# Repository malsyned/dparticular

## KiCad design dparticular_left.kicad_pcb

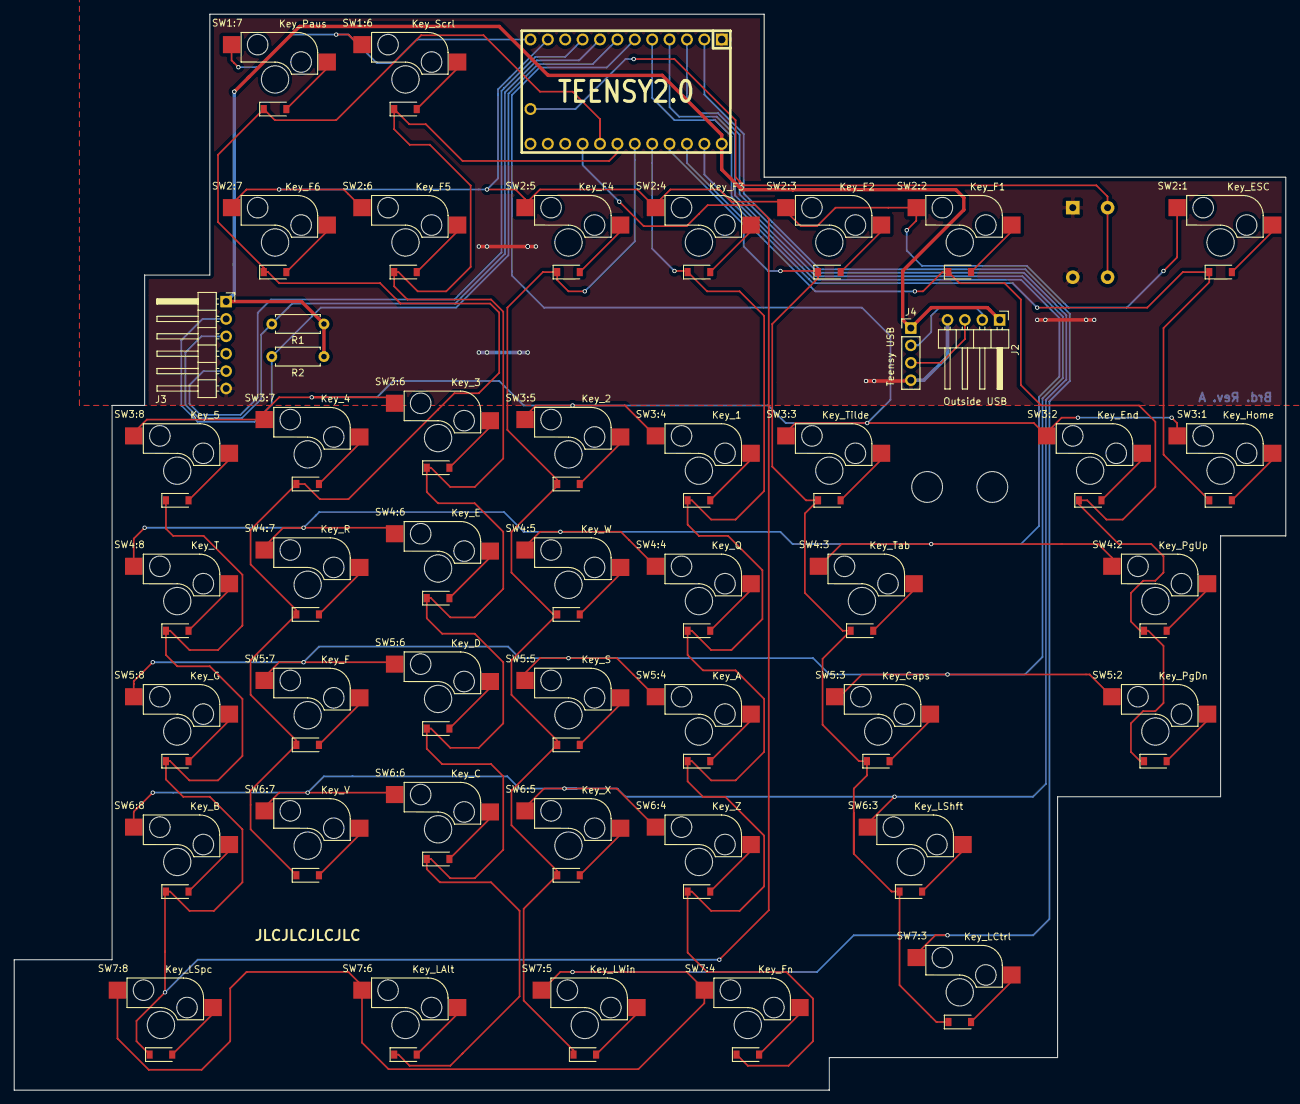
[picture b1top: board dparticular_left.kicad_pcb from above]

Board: 2 copper layers, 185.7 x 157.2 mm, 51 parts (1 on the bottom side), 65 nets.

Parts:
H1: USB Strain L; MountingHole_4.5mm
H2: USB Strain R; MountingHole_4.5mm
J2: Outside USB; PinHeader_1x04_P2.54mm_Horizontal
J3: To Right Hand; PinHeader_1x06_P2.54mm_Horizontal
J4: Teensy USB; PinHeader_1x04_P2.54mm_Vertical
R1, R2: 4.7k; R_Axial_DIN0207_L6.3mm_D2.5mm_P7.62mm_Horizontal
SW1: Reset; JB15KP-2A
SW1:6: Key_Scrl; MX_W_DIODE
SW1:7: Key_Paus; MX_W_DIODE
SW2:1: Key_ESC; MX_W_DIODE
SW2:2: Key_F1; MX_W_DIODE
SW2:3: Key_F2; MX_W_DIODE
SW2:4: Key_F3; MX_W_DIODE
SW2:5: Key_F4; MX_W_DIODE
SW2:6: Key_F5; MX_W_DIODE
SW2:7: Key_F6; MX_W_DIODE
SW3:1: Key_Home; MX_W_DIODE
SW3:2: Key_End; MX_W_DIODE
SW3:3: Key_Tilde; MX_W_DIODE
SW3:4: Key_1; MX_W_DIODE
SW3:5: Key_2; MX_W_DIODE
SW3:6: Key_3; MX_W_DIODE
SW3:7: Key_4; MX_W_DIODE
SW3:8: Key_5; MX_W_DIODE
SW4:2: Key_PgUp; MX_W_DIODE
SW4:3: Key_Tab; MX_W_DIODE
SW4:4: Key_Q; MX_W_DIODE
SW4:5: Key_W; MX_W_DIODE
SW4:6: Key_E; MX_W_DIODE
SW4:7: Key_R; MX_W_DIODE
SW4:8: Key_T; MX_W_DIODE
SW5:2: Key_PgDn; MX_W_DIODE
SW5:3: Key_Caps; MX_W_DIODE
SW5:4: Key_A; MX_W_DIODE
SW5:5: Key_S; MX_W_DIODE
SW5:6: Key_D; MX_W_DIODE
SW5:7: Key_F; MX_W_DIODE
SW5:8: Key_G; MX_W_DIODE
SW6:3: Key_LShft; MX_W_DIODE
SW6:4: Key_Z; MX_W_DIODE
SW6:5: Key_X; MX_W_DIODE
SW6:6: Key_C; MX_W_DIODE
SW6:7: Key_V; MX_W_DIODE
SW6:8: Key_B; MX_W_DIODE
SW7:3: Key_LCtrl; MX_W_DIODE
SW7:4: Key_Fn; MX_W_DIODE
SW7:5: Key_LWin; MX_W_DIODE
SW7:6: Key_LAlt; MX_W_DIODE
SW7:8: Key_LSpc; MX_W_DIODE
U2: TEENSY2.0; TEENSY_2.0_EDGES_ONLY

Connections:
+5V: J2.1, J3.1, J4.1, R1.1, R2.1, U2.29
/COL1: SW2:1.4, SW3:1.4, U2.28
/COL2: SW2:2.4, SW3:2.4, SW4:2.4, SW5:2.4, U2.27
/COL3: SW2:3.4, SW3:3.4, SW4:3.4, SW5:3.4, SW6:3.4, SW7:3.4, U2.26
/COL4: SW2:4.4, SW3:4.4, SW4:4.4, SW5:4.4, SW6:4.4, SW7:4.4, U2.25
/COL5: SW2:5.4, SW3:5.4, SW4:5.4, SW5:5.4, SW6:5.4, SW7:5.4, U2.24
/COL6: SW1:6.4, SW2:6.4, SW3:6.4, SW4:6.4, SW5:6.4, SW6:6.4, SW7:6.4, U2.23
/COL7: SW1:7.4, SW2:7.4, SW3:7.4, SW4:7.4, SW5:7.4, SW6:7.4, U2.22
/COL8: SW3:8.4, SW4:8.4, SW5:8.4, SW6:8.4, SW7:8.4, U2.21
/LED_D: J3.5, U2.9
/ROW1: SW1:6.1, SW1:7.1, U2.12
/ROW2: SW2:1.1, SW2:2.1, SW2:3.1, SW2:4.1, SW2:5.1, SW2:6.1, SW2:7.1, U2.11
/ROW3: SW3:1.1, SW3:2.1, SW3:3.1, SW3:4.1, SW3:5.1, SW3:6.1, SW3:7.1, SW3:8.1, U2.6
/ROW4: SW4:2.1, SW4:3.1, SW4:4.1, SW4:5.1, SW4:6.1, SW4:7.1, SW4:8.1, U2.5
/ROW5: SW5:2.1, SW5:3.1, SW5:4.1, SW5:5.1, SW5:6.1, SW5:7.1, SW5:8.1, U2.4
/ROW6: SW6:3.1, SW6:4.1, SW6:5.1, SW6:6.1, SW6:7.1, SW6:8.1, U2.3
/ROW7: SW7:3.1, SW7:4.1, SW7:5.1, SW7:6.1, SW7:8.1, U2.2
/SCL: J3.2, R2.2, U2.7
/SDA: J3.3, R1.2, U2.8
/USB_DN: J2.2, J4.2
/USB_DP: J2.3, J4.3
GND: J2.4, J3.6, J4.4, SW1.1, SW1.2, U2.1
unnamed: SW1.3, SW1.4, U2.16
unnamed: SW1:6.2, SW1:6.3
unnamed: SW1:7.2, SW1:7.3
unnamed: SW2:1.2, SW2:1.3
unnamed: SW2:2.2, SW2:2.3
unnamed: SW2:3.2, SW2:3.3
unnamed: SW2:4.2, SW2:4.3
unnamed: SW2:5.2, SW2:5.3
unnamed: SW2:6.2, SW2:6.3
unnamed: SW2:7.2, SW2:7.3
unnamed: SW3:1.2, SW3:1.3
unnamed: SW3:2.2, SW3:2.3
unnamed: SW3:3.2, SW3:3.3
unnamed: SW3:4.2, SW3:4.3
unnamed: SW3:5.2, SW3:5.3
unnamed: SW3:6.2, SW3:6.3
unnamed: SW3:7.2, SW3:7.3
unnamed: SW3:8.2, SW3:8.3
unnamed: SW4:2.2, SW4:2.3
unnamed: SW4:3.2, SW4:3.3
unnamed: SW4:4.2, SW4:4.3
unnamed: SW4:5.2, SW4:5.3
unnamed: SW4:6.2, SW4:6.3
unnamed: SW4:7.2, SW4:7.3
unnamed: SW4:8.2, SW4:8.3
unnamed: SW5:2.2, SW5:2.3
unnamed: SW5:3.2, SW5:3.3
unnamed: SW5:4.2, SW5:4.3
unnamed: SW5:5.2, SW5:5.3
unnamed: SW5:6.2, SW5:6.3
unnamed: SW5:7.2, SW5:7.3
unnamed: SW5:8.2, SW5:8.3
unnamed: SW6:3.2, SW6:3.3
unnamed: SW6:4.2, SW6:4.3
unnamed: SW6:5.2, SW6:5.3
unnamed: SW6:6.2, SW6:6.3
unnamed: SW6:7.2, SW6:7.3
unnamed: SW6:8.2, SW6:8.3
unnamed: SW7:3.2, SW7:3.3
unnamed: SW7:4.2, SW7:4.3
unnamed: SW7:5.2, SW7:5.3
unnamed: SW7:6.2, SW7:6.3
unnamed: SW7:8.2, SW7:8.3

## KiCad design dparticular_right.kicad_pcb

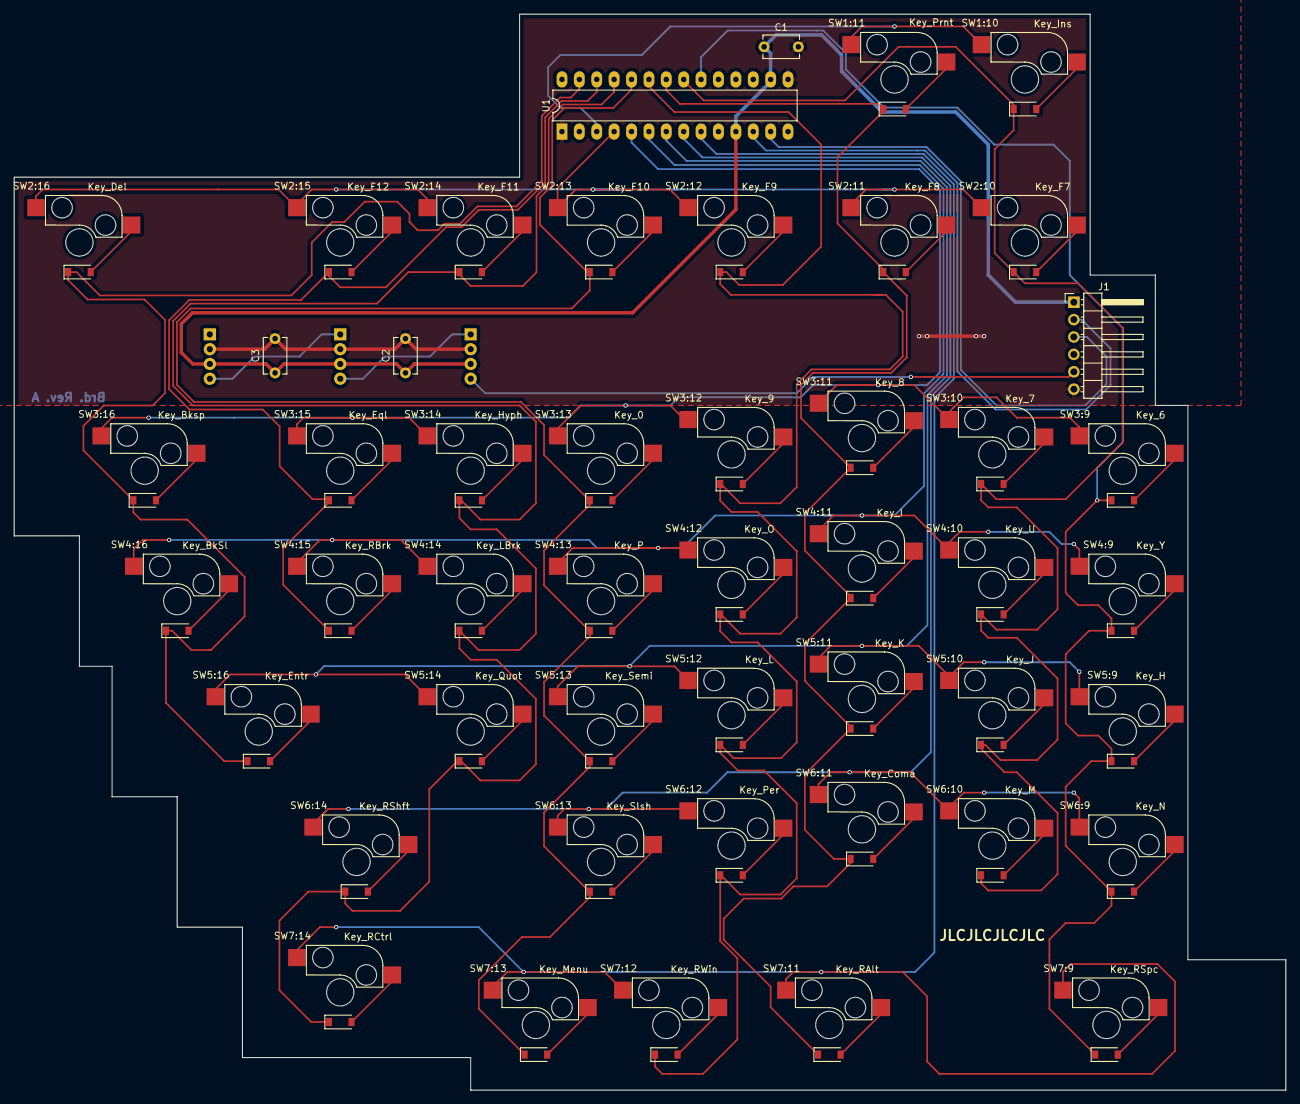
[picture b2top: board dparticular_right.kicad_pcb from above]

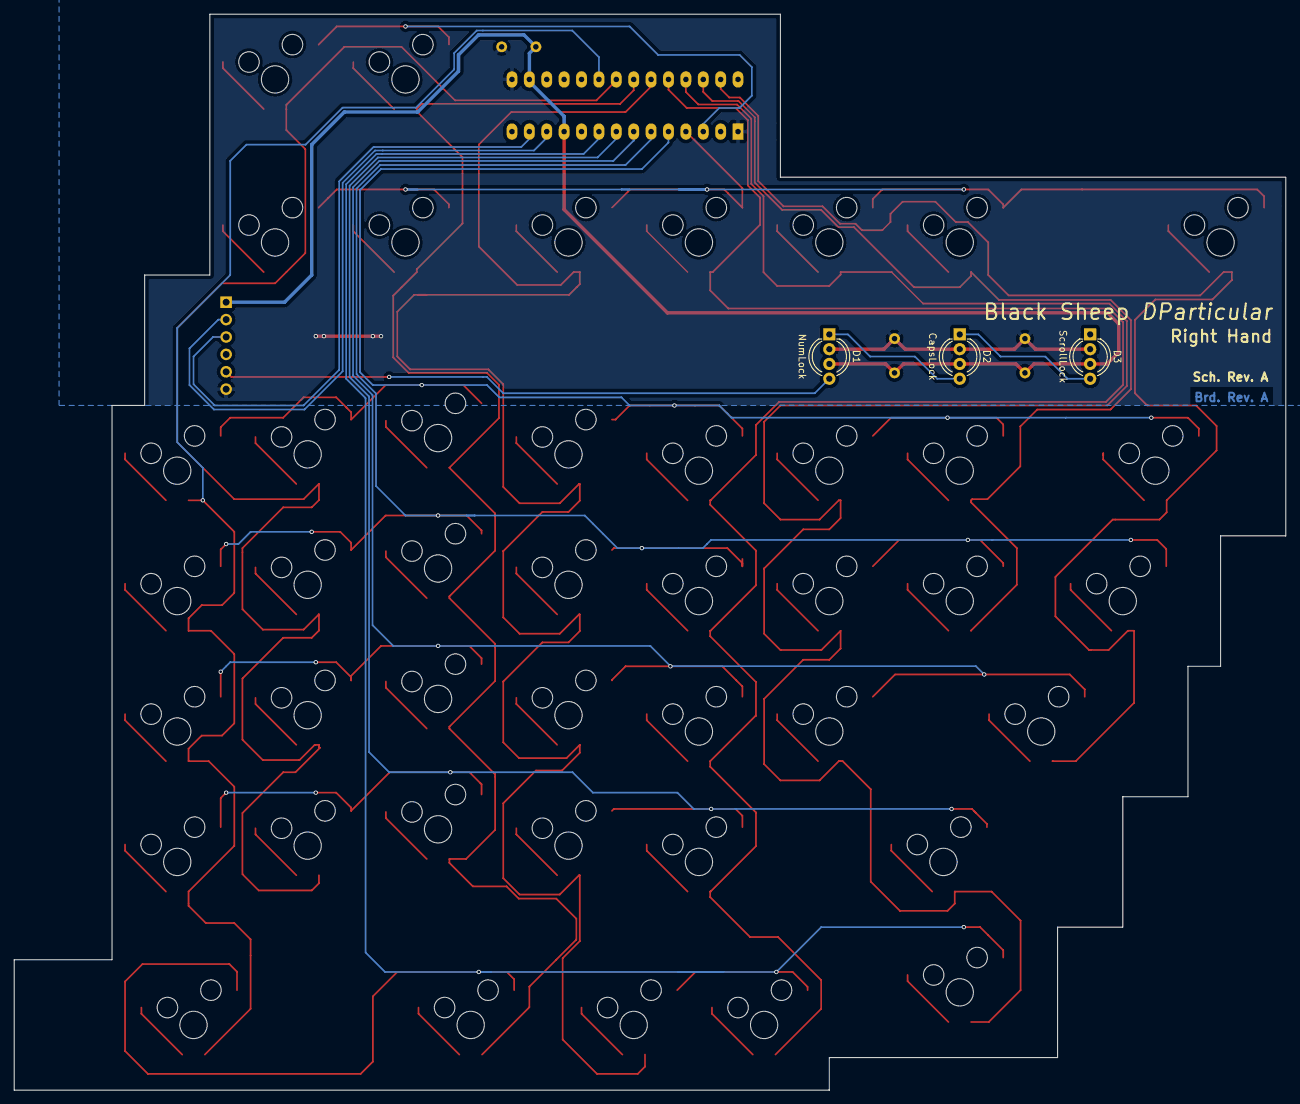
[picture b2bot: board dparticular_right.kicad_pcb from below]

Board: 2 copper layers, 185.7 x 157.2 mm, 51 parts (3 on the bottom side), 65 nets.

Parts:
C1, C2, C3: 0.1uF; C_Disc_D5.1mm_W3.2mm_P5.00mm
D1: NumLock; LED_D5.0mm-4_RGB_Wide_Pins
D2: CapsLock; LED_D5.0mm-4_RGB_Wide_Pins
D3: ScrollLock; LED_D5.0mm-4_RGB_Wide_Pins
J1: To Left Hand; PinHeader_1x06_P2.54mm_Horizontal
SW1:10: Key_Ins; MX_W_DIODE
SW1:11: Key_Prnt; MX_W_DIODE
SW2:10: Key_F7; MX_W_DIODE
SW2:11: Key_F8; MX_W_DIODE
SW2:12: Key_F9; MX_W_DIODE
SW2:13: Key_F10; MX_W_DIODE
SW2:14: Key_F11; MX_W_DIODE
SW2:15: Key_F12; MX_W_DIODE
SW2:16: Key_Del; MX_W_DIODE
SW3:9: Key_6; MX_W_DIODE
SW3:10: Key_7; MX_W_DIODE
SW3:11: Key_8; MX_W_DIODE
SW3:12: Key_9; MX_W_DIODE
SW3:13: Key_0; MX_W_DIODE
SW3:14: Key_Hyph; MX_W_DIODE
SW3:15: Key_Eql; MX_W_DIODE
SW3:16: Key_Bksp; MX_W_DIODE
SW4:9: Key_Y; MX_W_DIODE
SW4:10: Key_U; MX_W_DIODE
SW4:11: Key_I; MX_W_DIODE
SW4:12: Key_O; MX_W_DIODE
SW4:13: Key_P; MX_W_DIODE
SW4:14: Key_LBrk; MX_W_DIODE
SW4:15: Key_RBrk; MX_W_DIODE
SW4:16: Key_BkSl; MX_W_DIODE
SW5:9: Key_H; MX_W_DIODE
SW5:10: Key_J; MX_W_DIODE
SW5:11: Key_K; MX_W_DIODE
SW5:12: Key_L; MX_W_DIODE
SW5:13: Key_Semi; MX_W_DIODE
SW5:14: Key_Quot; MX_W_DIODE
SW5:16: Key_Entr; MX_W_DIODE
SW6:9: Key_N; MX_W_DIODE
SW6:10: Key_M; MX_W_DIODE
SW6:11: Key_Coma; MX_W_DIODE
SW6:12: Key_Per; MX_W_DIODE
SW6:13: Key_Slsh; MX_W_DIODE
SW6:14: Key_RShft; MX_W_DIODE
SW7:9: Key_RSpc; MX_W_DIODE
SW7:11: Key_RAlt; MX_W_DIODE
SW7:12: Key_RWin; MX_W_DIODE
SW7:13: Key_Menu; MX_W_DIODE
SW7:14: Key_RCtrl; MX_W_DIODE
U1: MCP23018; DIP-28_W7.62mm_LongPads

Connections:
+5V: C1.1, C2.1, C3.1, D1.3, D2.3, D3.3, J1.1, U1.11, U1.16
/COL9: SW3:9.4, SW4:9.4, SW5:9.4, SW6:9.4, SW7:9.4, U1.20
/COL10: SW1:10.4, SW2:10.4, SW3:10.4, SW4:10.4, SW5:10.4, SW6:10.4, U1.21
/COL11: SW1:11.4, SW2:11.4, SW3:11.4, SW4:11.4, SW5:11.4, SW6:11.4, SW7:11.4, U1.22
/COL12: SW2:12.4, SW3:12.4, SW4:12.4, SW5:12.4, SW6:12.4, SW7:12.4, U1.23
/COL13: SW2:13.4, SW3:13.4, SW4:13.4, SW5:13.4, SW6:13.4, SW7:13.4, U1.24
/COL14: SW2:14.4, SW3:14.4, SW4:14.4, SW5:14.4, SW6:14.4, SW7:14.4, U1.25
/COL15: SW2:15.4, SW3:15.4, SW4:15.4, U1.26
/COL16: SW2:16.4, SW3:16.4, SW4:16.4, SW5:16.4, U1.27
/LED_D: D1.4, J1.5
/ROW1: SW1:10.1, SW1:11.1, U1.3
/ROW2: SW2:10.1, SW2:11.1, SW2:12.1, SW2:13.1, SW2:14.1, SW2:15.1, SW2:16.1, U1.4
/ROW3: SW3:9.1, SW3:10.1, SW3:11.1, SW3:12.1, SW3:13.1, SW3:14.1, SW3:15.1, SW3:16.1, U1.5
/ROW4: SW4:9.1, SW4:10.1, SW4:11.1, SW4:12.1, SW4:13.1, SW4:14.1, SW4:15.1, SW4:16.1, U1.6
/ROW5: SW5:9.1, SW5:10.1, SW5:11.1, SW5:12.1, SW5:13.1, SW5:14.1, SW5:16.1, U1.7
/ROW6: SW6:9.1, SW6:10.1, SW6:11.1, SW6:12.1, SW6:13.1, SW6:14.1, U1.8
/ROW7: SW7:9.1, SW7:11.1, SW7:12.1, SW7:13.1, SW7:14.1, U1.9
/SCL: J1.2, U1.12
/SDA: J1.3, U1.13
GND: C1.2, C2.2, C3.2, D1.2, D2.2, D3.2, J1.6, U1.1, U1.15
unnamed: D1.1, D2.4
unnamed: D2.1, D3.4
unnamed: SW1:10.2, SW1:10.3
unnamed: SW1:11.2, SW1:11.3
unnamed: SW2:10.2, SW2:10.3
unnamed: SW2:11.2, SW2:11.3
unnamed: SW2:12.2, SW2:12.3
unnamed: SW2:13.2, SW2:13.3
unnamed: SW2:14.2, SW2:14.3
unnamed: SW2:15.2, SW2:15.3
unnamed: SW2:16.2, SW2:16.3
unnamed: SW3:9.2, SW3:9.3
unnamed: SW3:10.2, SW3:10.3
unnamed: SW3:11.2, SW3:11.3
unnamed: SW3:12.2, SW3:12.3
unnamed: SW3:13.2, SW3:13.3
unnamed: SW3:14.2, SW3:14.3
unnamed: SW3:15.2, SW3:15.3
unnamed: SW3:16.2, SW3:16.3
unnamed: SW4:9.2, SW4:9.3
unnamed: SW4:10.2, SW4:10.3
unnamed: SW4:11.2, SW4:11.3
unnamed: SW4:12.2, SW4:12.3
unnamed: SW4:13.2, SW4:13.3
unnamed: SW4:14.2, SW4:14.3
unnamed: SW4:15.2, SW4:15.3
unnamed: SW4:16.2, SW4:16.3
unnamed: SW5:9.2, SW5:9.3
unnamed: SW5:10.2, SW5:10.3
unnamed: SW5:11.2, SW5:11.3
unnamed: SW5:12.2, SW5:12.3
unnamed: SW5:13.2, SW5:13.3
unnamed: SW5:14.2, SW5:14.3
unnamed: SW5:16.2, SW5:16.3
unnamed: SW6:9.2, SW6:9.3
unnamed: SW6:10.2, SW6:10.3
unnamed: SW6:11.2, SW6:11.3
unnamed: SW6:12.2, SW6:12.3
unnamed: SW6:13.2, SW6:13.3
unnamed: SW6:14.2, SW6:14.3
unnamed: SW7:9.2, SW7:9.3
unnamed: SW7:11.2, SW7:11.3
unnamed: SW7:12.2, SW7:12.3
unnamed: SW7:13.2, SW7:13.3
unnamed: SW7:14.2, SW7:14.3

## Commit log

2020-06-24 DParticular initial commit, incomplete schematic
2020-07-01 Complete rough schematic
2020-07-06 Add enclosure 3D model
2020-07-06 Schematic revisions; first attempt at layout
2020-07-07 Beginning of separate right board project
2020-07-07 Preliminary placements for right hand
2020-07-07 Preliminary placements for left hand
2020-07-07 Deleted combined net and pcb
2020-07-07 Fixed footprints on switches and headers
2020-07-07 Edge cuts, net list exports
2020-07-07 .gitignore: kicad autosave files
2020-07-07 LED orientation and wiring
2020-07-08 LED labeling, schematic cosmetics
2020-07-08 Design rules compatible with common prototype board manufacturers
    Maximums that work with JLCPCB, ALLPCB, and Elecrow
2020-07-08 right hand PCB: Column traces
2020-07-08 Fix LED name order
2020-07-09 Right hand completed layout
2020-07-09 Left hand: updated solder mask design rules
2020-07-09 Moved USB headers to reduce width of top rectangle
2020-07-09 Remove .net files from repository
2020-07-09 Right hand: don't run traces between pads
2020-07-09 Right hand: eliminate right angles in columns 9 and 10
2020-07-09 Right hand: eliminate right angles in remaining columns
2020-07-09 Right hand: Eliminate all remaining right angles
2020-07-09 MX_W_DIODE: Cleaned up silk screen for hot plug socket
2020-07-09 Left hand: Changed uC pin assignments; Routed diode tracks and power rail
2020-07-09 Left hand: Routed columns
2020-07-09 Left hand: Completed routing
2020-07-09 Left hand: Cleaned up ground paths
2020-07-10 enclosure: 1/16" margin around PCBs
2020-07-10 enclosure: clean up inner edge
2020-07-10 enclosure: tweaked palm rest dimensions and rear margin
2020-07-10 enclosure: screw position sketch
2020-07-10 enclosure: threaded inserts
2020-07-10 enclosure: screw cutout cylinders
2020-07-10 enclosure: solid plate with screw holes
2020-07-10 Right hand pcb: Move LEDs half a key to the left
    This let's them be more visible between keycaps from a shallow viewing
    angle.
2020-07-10 Right hand PCB: Move traces farther away from drill holes
2020-07-14 PCBs: 3D models for Teensy 2.0 and MX sockets & diodes
2020-07-14 Left Hand PCB: Remove 3D header for Teensy USB solder points
2020-07-18 Left hand PCB: match fill zone size to right hand
2020-07-18 Teensy 2.0 Footprint: Assemble 3D model from upstream components
2020-07-18 MX_W_DIODE: Tweak socket 3D model scaling to compensate for upstream error
2020-07-19 enclosure: actually solid plate with screw holes
2020-07-19 enclosure: plate: clearance and corner radius
2020-07-19 enclosure: store distance from screw to edges in spreadsheet
2020-07-19 enclosure: threaded insert drill guides
2020-07-19 enclosure: Right top solid with drill holes
2020-07-19 enclosure: import and position latest PCB STEP files
2020-07-19 enclosure: mirror right solid plate and top to left half
2020-07-19 enclosure: holes in top and plate for lock status LEDs
    The offset of the centers from the F-keys row was hand-calculated by
    examining both the PCB layout and the footprint for the LED in question.
    If that part of the PCB layout changes, this will have to be
    hand-recomputed.
2020-07-19 enclosure: round outside edges of top pieces
    I removed the PCBs in this commit as well. Some STEP setting on my
    desktop was causing them to be huge and Github was throwing warnings.
2020-07-19 enclosure: Cutouts in plates and tops
2020-07-21 enclosure: adjust border after pleather experiments
2020-07-22 Left PCB: Mounting holes for USB strain relief zip ties
2020-07-25 Left Hand PCB: Reset switch for Teensy 2.0
2020-07-25 Left Hand PCB: Shorter switch, properly positioned
2020-07-26 Teensy 2.0 3D Model: Single pin (RST) connector for back edge
2020-07-26 Left Hand PCB: Move traces out from under Reset switch
2020-07-26 Reset Switch: Use schematic symbol with correct pinout
2020-07-26 enclosure: Reset switch cuts in left plate and top
2020-07-26 Reset Switch: Move between ESC and F1
2020-07-26 Right Hand PCB: Make some space for potential future drill holes
2020-07-27 enclosure: Adjust margins and enclosure width
    The front margin is reduced from 0.33" to 0.25"
    The side margin is moved and increased to fit potential future arrow keys
    The enclosure wall width is decreased from 3/8" to 1/4"
2020-07-28 enclosure: give the left half mirror a real name
2020-07-28 enclosure: Add flat face to front edge
2020-07-28 enclosure: initial sketch of palm pad pockets
2020-07-28 enclosure palm pad cuts: round corners
2020-07-30 Right Hand PCB: Moved LEDs half a key right and centered them vertically
    I made this change after discovering that, head on in perspective view,
    the LEDs are more visible centered on the keys than on the key edges.
2020-07-30 Righ Hand PCB: improved ground plane coverage
2020-07-31 enclosure: Palm pad dimensions referenced to actual measurements
    This allowed me to confidently parameterize a lot more of the dimensions
    that make up the front into the spreadsheet.
2020-07-31 enclosure: backed out to before wrong fillet. Right fillet freezes FreeCAD
2020-08-02 enclosure: snub nose; work around fillet crash
2020-08-03 enclosure: tighten palm pad tolerances
2020-08-03 enclosure: small dimension adjustments along the palm rest
2020-08-03 enclosure: Fillets on inner corners of main pocket
2020-08-03 enclosure: extra clearance for PCB corners in cutout
2020-08-03 enclosure: Fix boundaries of top piece
2020-08-03 enclosure: Fillets on shallow part of main pocket
2020-08-03 Left Hand PCB: Harmonize inter-board ribbon header orientations
2020-08-05 Right Hand PCB: Tidying and ground fill expanding
2020-08-05 Right Hand Schematic: Deleted stray NC X
2020-08-05 Palm pad footprint: tweaks after comparing sketch printout with real unit
2020-08-07 enclosure: 1/2" end mill, 1/4" ball nose
2020-08-07 enclosure: bottom radius for shallow pocket
2020-08-07 enclosure: 20% safety margin on all functional fillets
2020-08-07 enclosure: Bigger cutout margin on inside edges
2020-08-07 enclosure: ensure pocket radii don't interfere with PCB corners
2020-08-07 enclosure: rounder nose
2020-08-07 enclosure: pocket radii >= 1/3 pocket depth
2020-08-07 enclosure: simplified palm pad cut fillet instructions
2020-08-08 enclosure: Reduce ball-nose fillets to exact size
    Per Doug Ruuska
2020-08-08 enclosure: Added back in some top edge fillets in 3D region
2020-08-09 PCBs: Clean up via line by line analysis
2020-08-09 PCBs: Move vias off silk screen
2020-08-09 PCBs: More proofreading and cleanup
2020-08-09 PCBs: Added JLC Order Number placeholders
2020-08-09 PCBs: Edge cuts to 6 mils for JLCPCB
2020-08-09 enclosure: Larger plate LED holes for lens shelf
2020-08-09 PCBs: US Letter page size
2020-08-09 Schematic: Filled in Title Block; USLetter page size
2020-08-09 PCBs: Filled in Title Block
2020-08-09 PCBs: Branding and revision IDs
2020-08-10 PCBs: Plotting options
2020-08-10 enclosure: sleeker nose sculpt
2020-08-11 Tops: 0.5mm Larger clearance to account for pocket fillet
2020-08-11 enclosure: TechDraw pages for first round of laser cut quoting
2020-08-12 enclosure: simplified switch plate cutouts
    According to nevin on geekhack, Kailh BOX switches don't work with the
    "MX Openable Cutout" and using simple squares saves money on laser
    cutting.
    https://geekhack.org/index.php?topic=108027.0
2020-08-12 enclosure: corrected rotation on left hand stabilizers
2020-08-12 enclosure: TechDraw pages for plates, second round of quoting
2020-08-13 tops and plates: vectors and dimension drawings
2020-08-14 Drawings: Flip and reorient for space; Add parts for guiding drill holes
2020-08-15 Top Drawing: More complete dimensional information
2020-08-15 Drawings: Link to base shapes via Facebinders
2020-08-21 Dimensioned drawings: ensure labels don't overlap in metric
2020-08-21 Right Plate: Enlarge LED cutouts to avoid shorting pins
2020-08-25 Kailh Socket: Fix 3D part orientation
2020-08-25 MX Footprint: Fix socket silkscreen
2020-08-25 enclosure: higher resolution palm pad sketch
2020-08-25 enclosure: actual palm pad photo; palm pad footprint tweaks
2020-08-25 Kailh Socket Footprint: Update PCBs from footprint
2020-09-19 enclosure: separate control of back thickness and side thickness
2020-09-29 enclosure: removed leather palm pads; reduced size front-to-back
2020-10-06 enclosure: convex palm rest
2020-10-07 enclosure: longer palm rest outside edges

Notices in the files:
dparticular_left.kicad_pcb:
License: CC BY-SA 4.0
